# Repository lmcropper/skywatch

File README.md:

# skywatch
BATTERY MANAGEMENT V1 (JST)

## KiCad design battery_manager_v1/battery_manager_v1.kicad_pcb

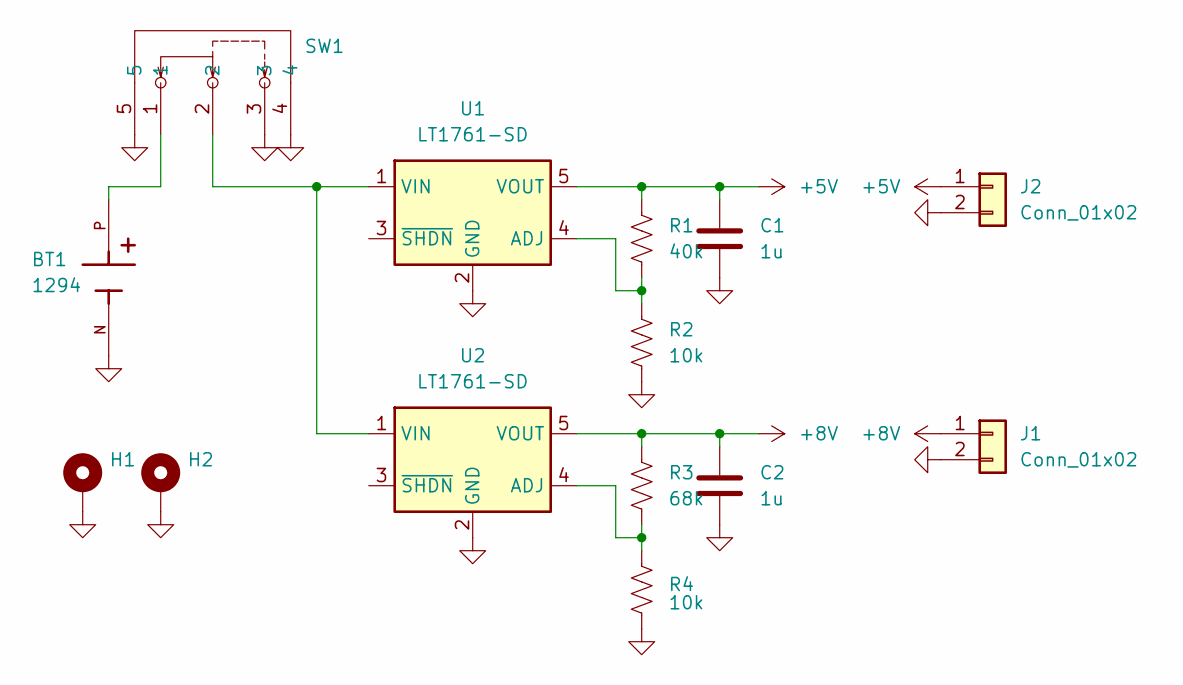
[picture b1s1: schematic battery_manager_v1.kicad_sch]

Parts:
BT1: 1294; BAT_1294; PARTREV C
C1, C2: 1u; C_0603_1608Metric
H1, H2: MountingHole_Pad; MountingHole_3.2mm_M3_DIN965_Pad_TopOnly
J1, J2: Conn_01x02; JST_PH_S2B-PH-K_1x02_P2.00mm_Horizontal
R1: 40k; R_0603_1608Metric
R2, R4: 10k; R_0603_1608Metric
R3: 68k; R_0603_1608Metric
SW1: SS-12F44-G5; SW-TH_SS-12F44-G5; LCSC Part C136718
U1, U2: LT1761-SD; TSOT-23-5

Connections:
+5V: C1.1, J2.1, R1.1, U1.5 (VOUT)
+8V: C2.1, J1.1, R3.1, U2.5 (VOUT)
GND: BT1.N, C1.2, C2.2, H1.1, H2.1, J1.2, J2.2, R2.2, R4.2, SW1.3, SW1.4, SW1.5, U1.2 (GND), U2.2 (GND)
unnamed: BT1.P, SW1.1
unnamed: R1.2, R2.1, U1.4 (ADJ)
unnamed: SW1.2, U1.1 (VIN), U2.1 (VIN)
unnamed: R3.2, R4.1, U2.4 (ADJ)

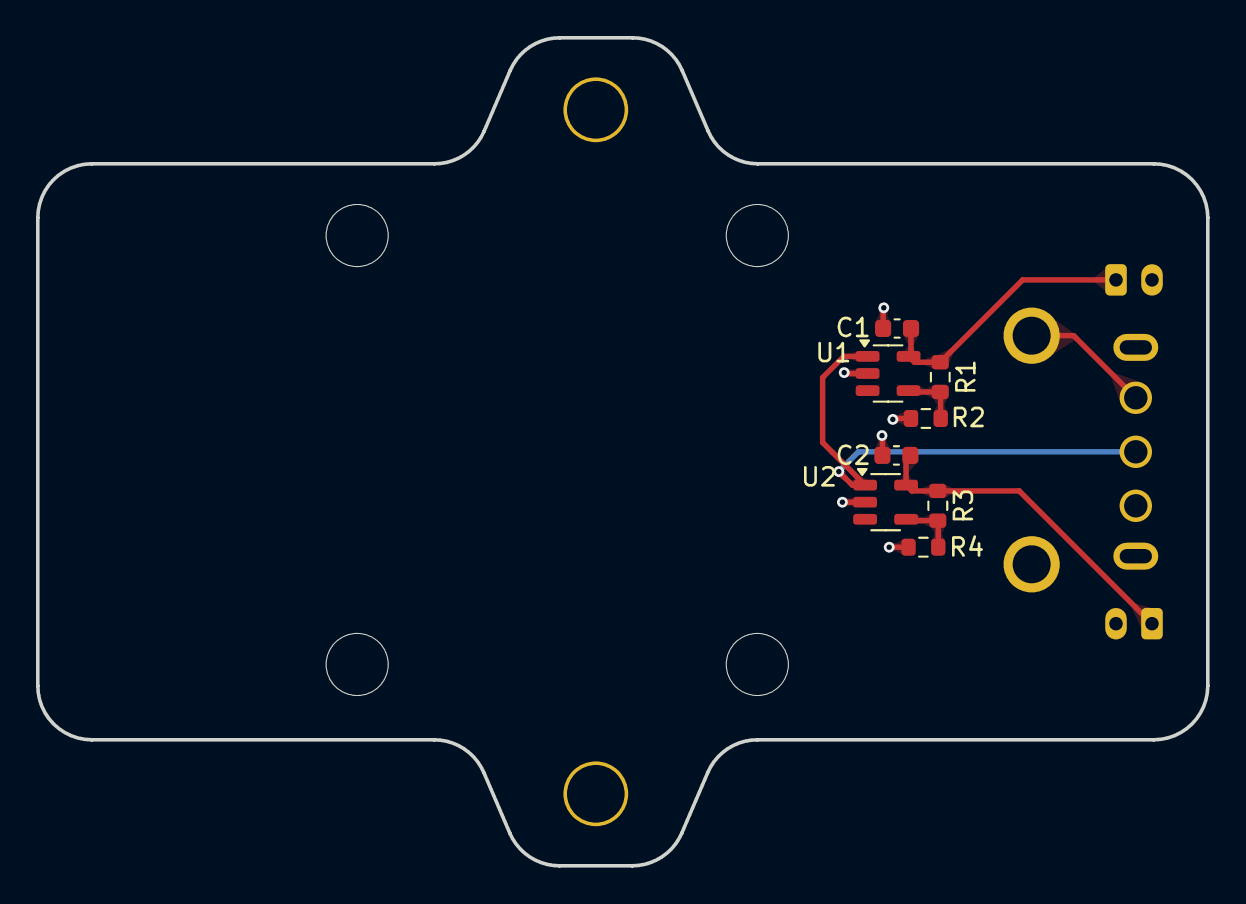
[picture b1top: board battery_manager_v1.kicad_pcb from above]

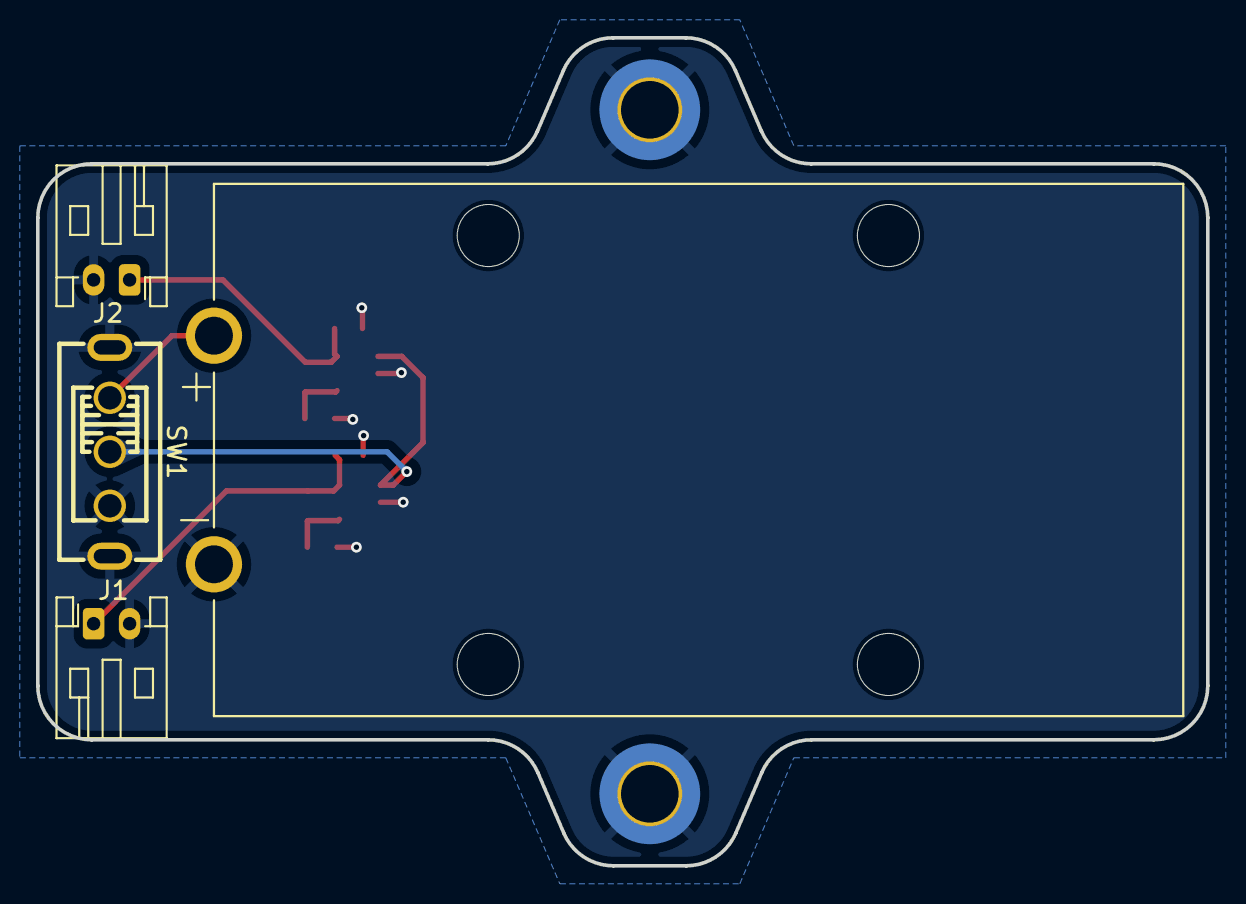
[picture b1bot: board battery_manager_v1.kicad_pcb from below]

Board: 2 copper layers, 65.0 x 46.0 mm, 14 parts (6 on the bottom side), 7 nets.

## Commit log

2024-11-06 Created KiCad Project
2024-11-06 Added Regulators etc.
2024-11-11 V1 Final Before Update to V2
2024-12-03 Updates and first creation of gerbers
2024-12-04 Stable Version with JST for modem PD
